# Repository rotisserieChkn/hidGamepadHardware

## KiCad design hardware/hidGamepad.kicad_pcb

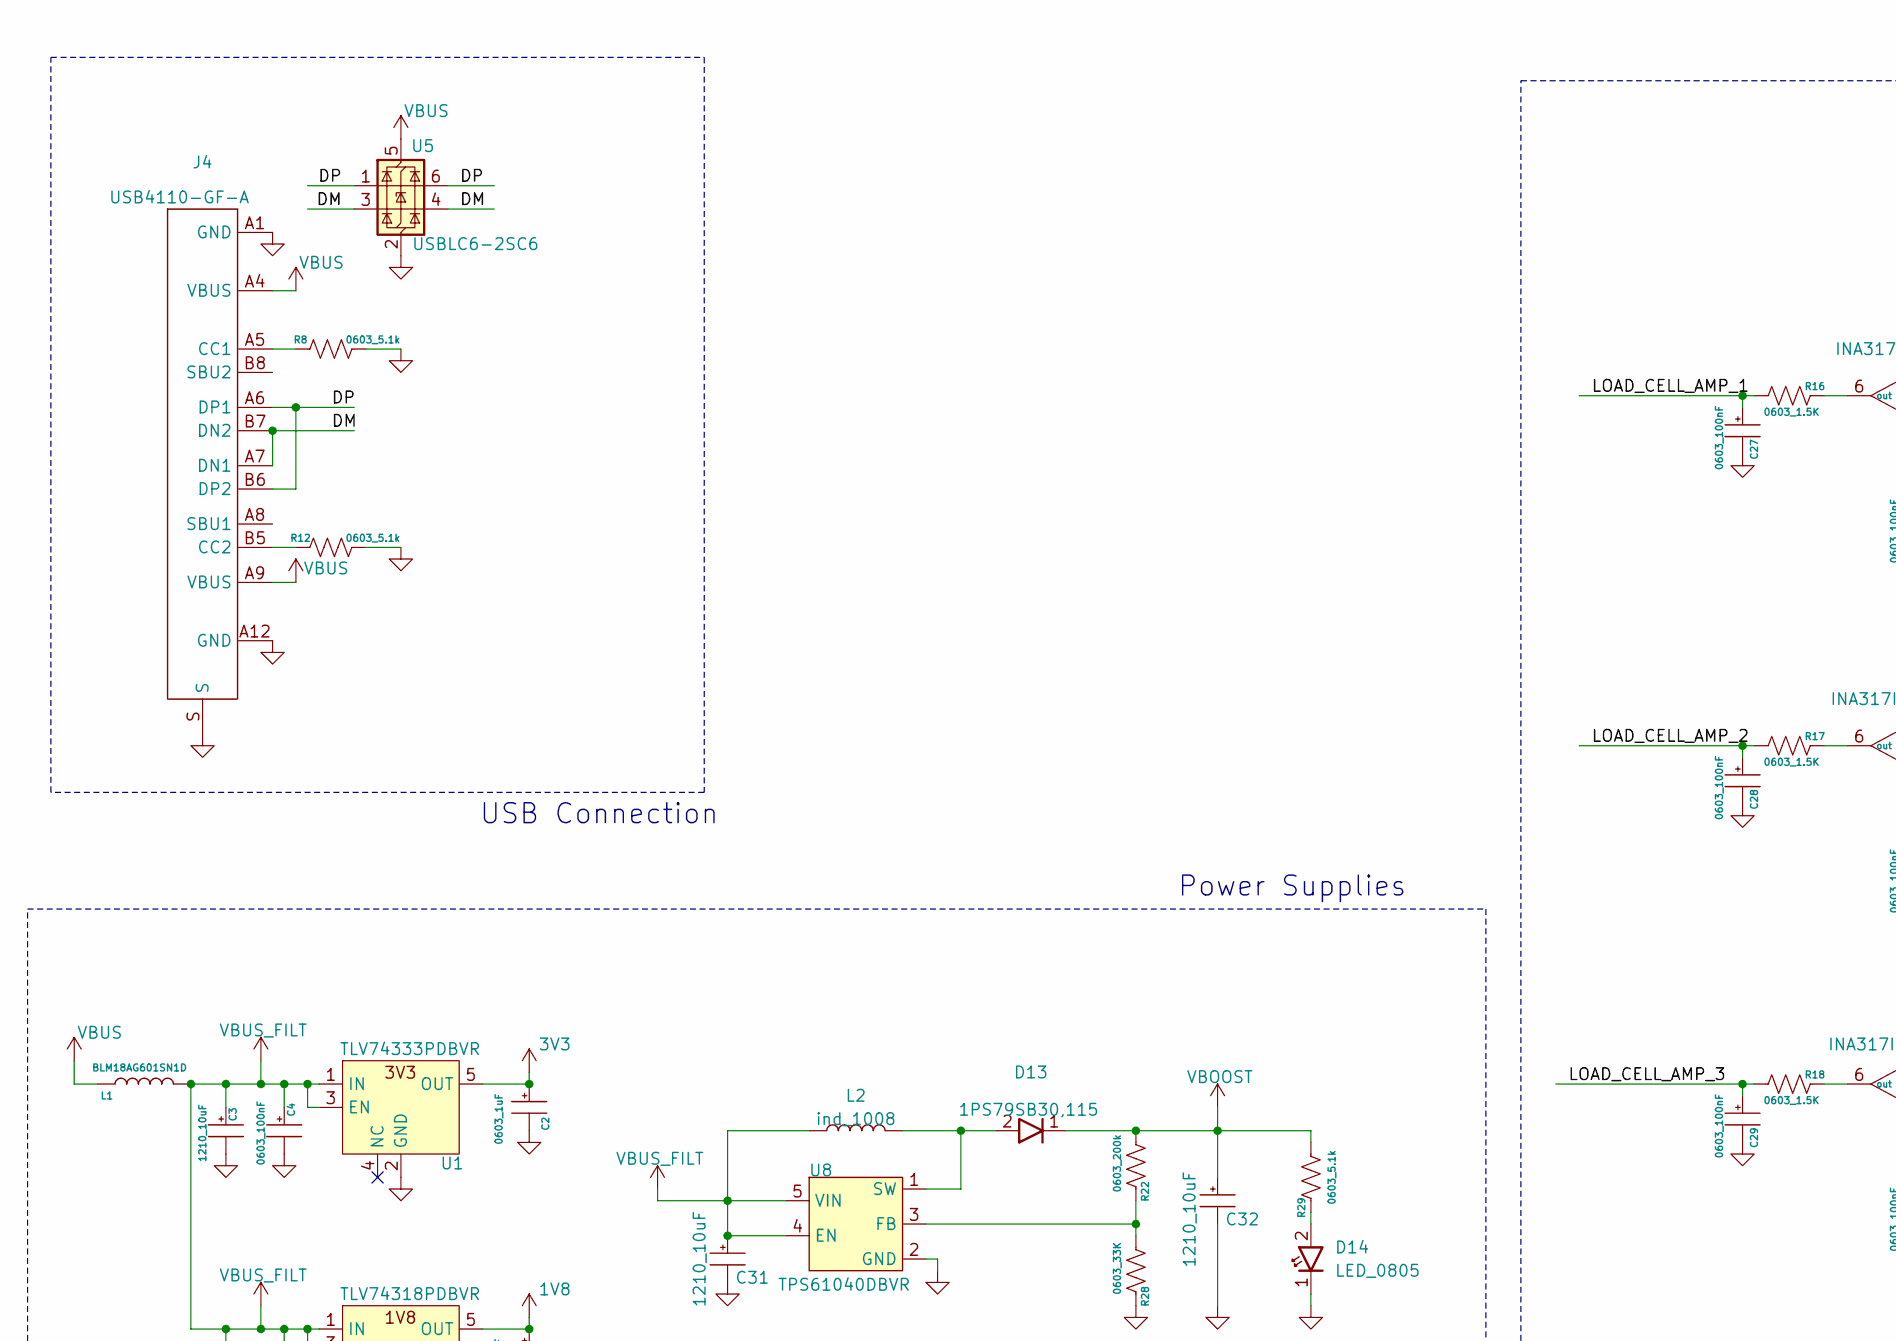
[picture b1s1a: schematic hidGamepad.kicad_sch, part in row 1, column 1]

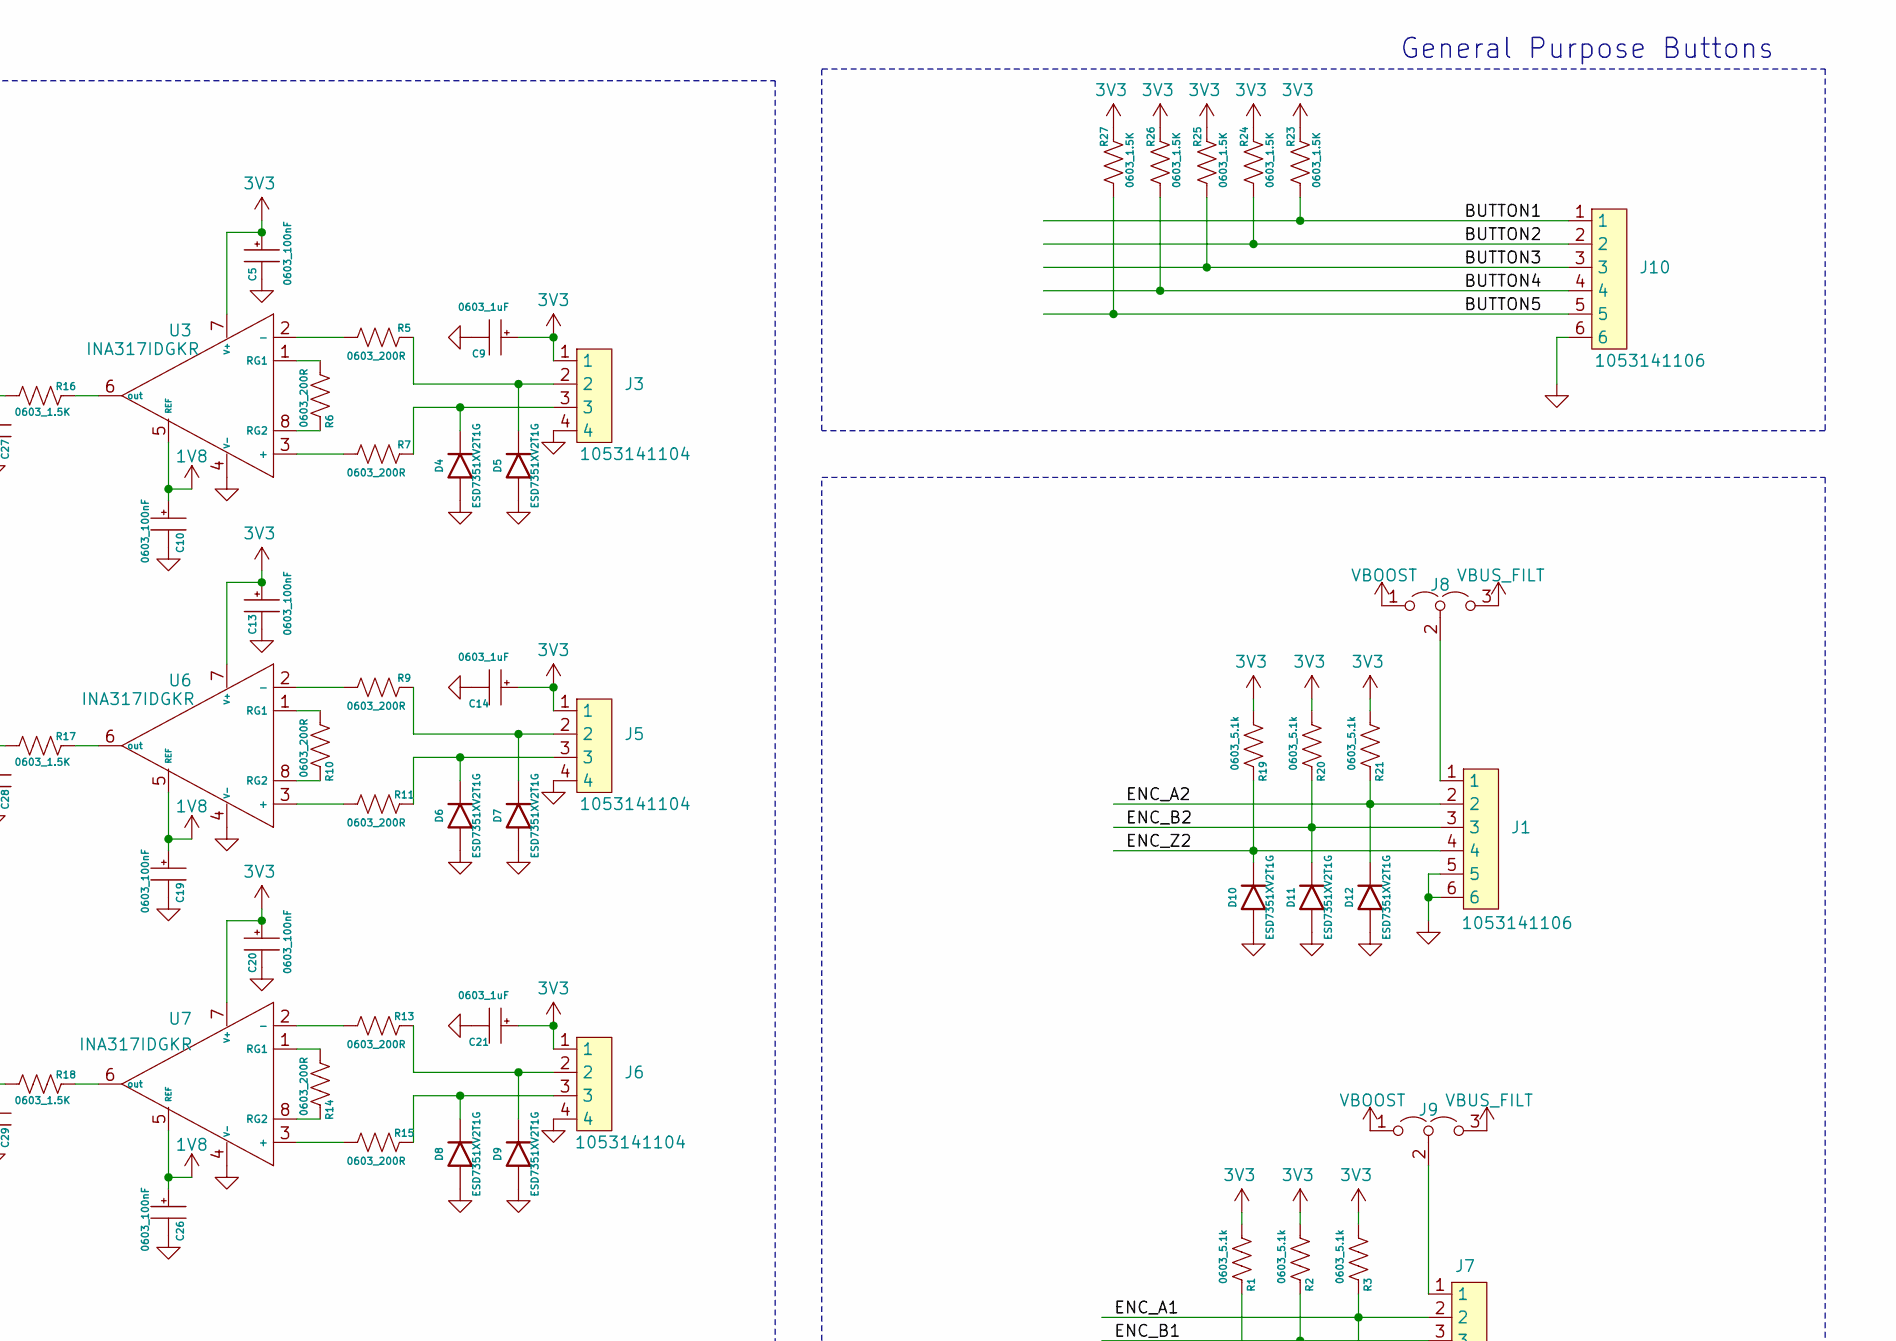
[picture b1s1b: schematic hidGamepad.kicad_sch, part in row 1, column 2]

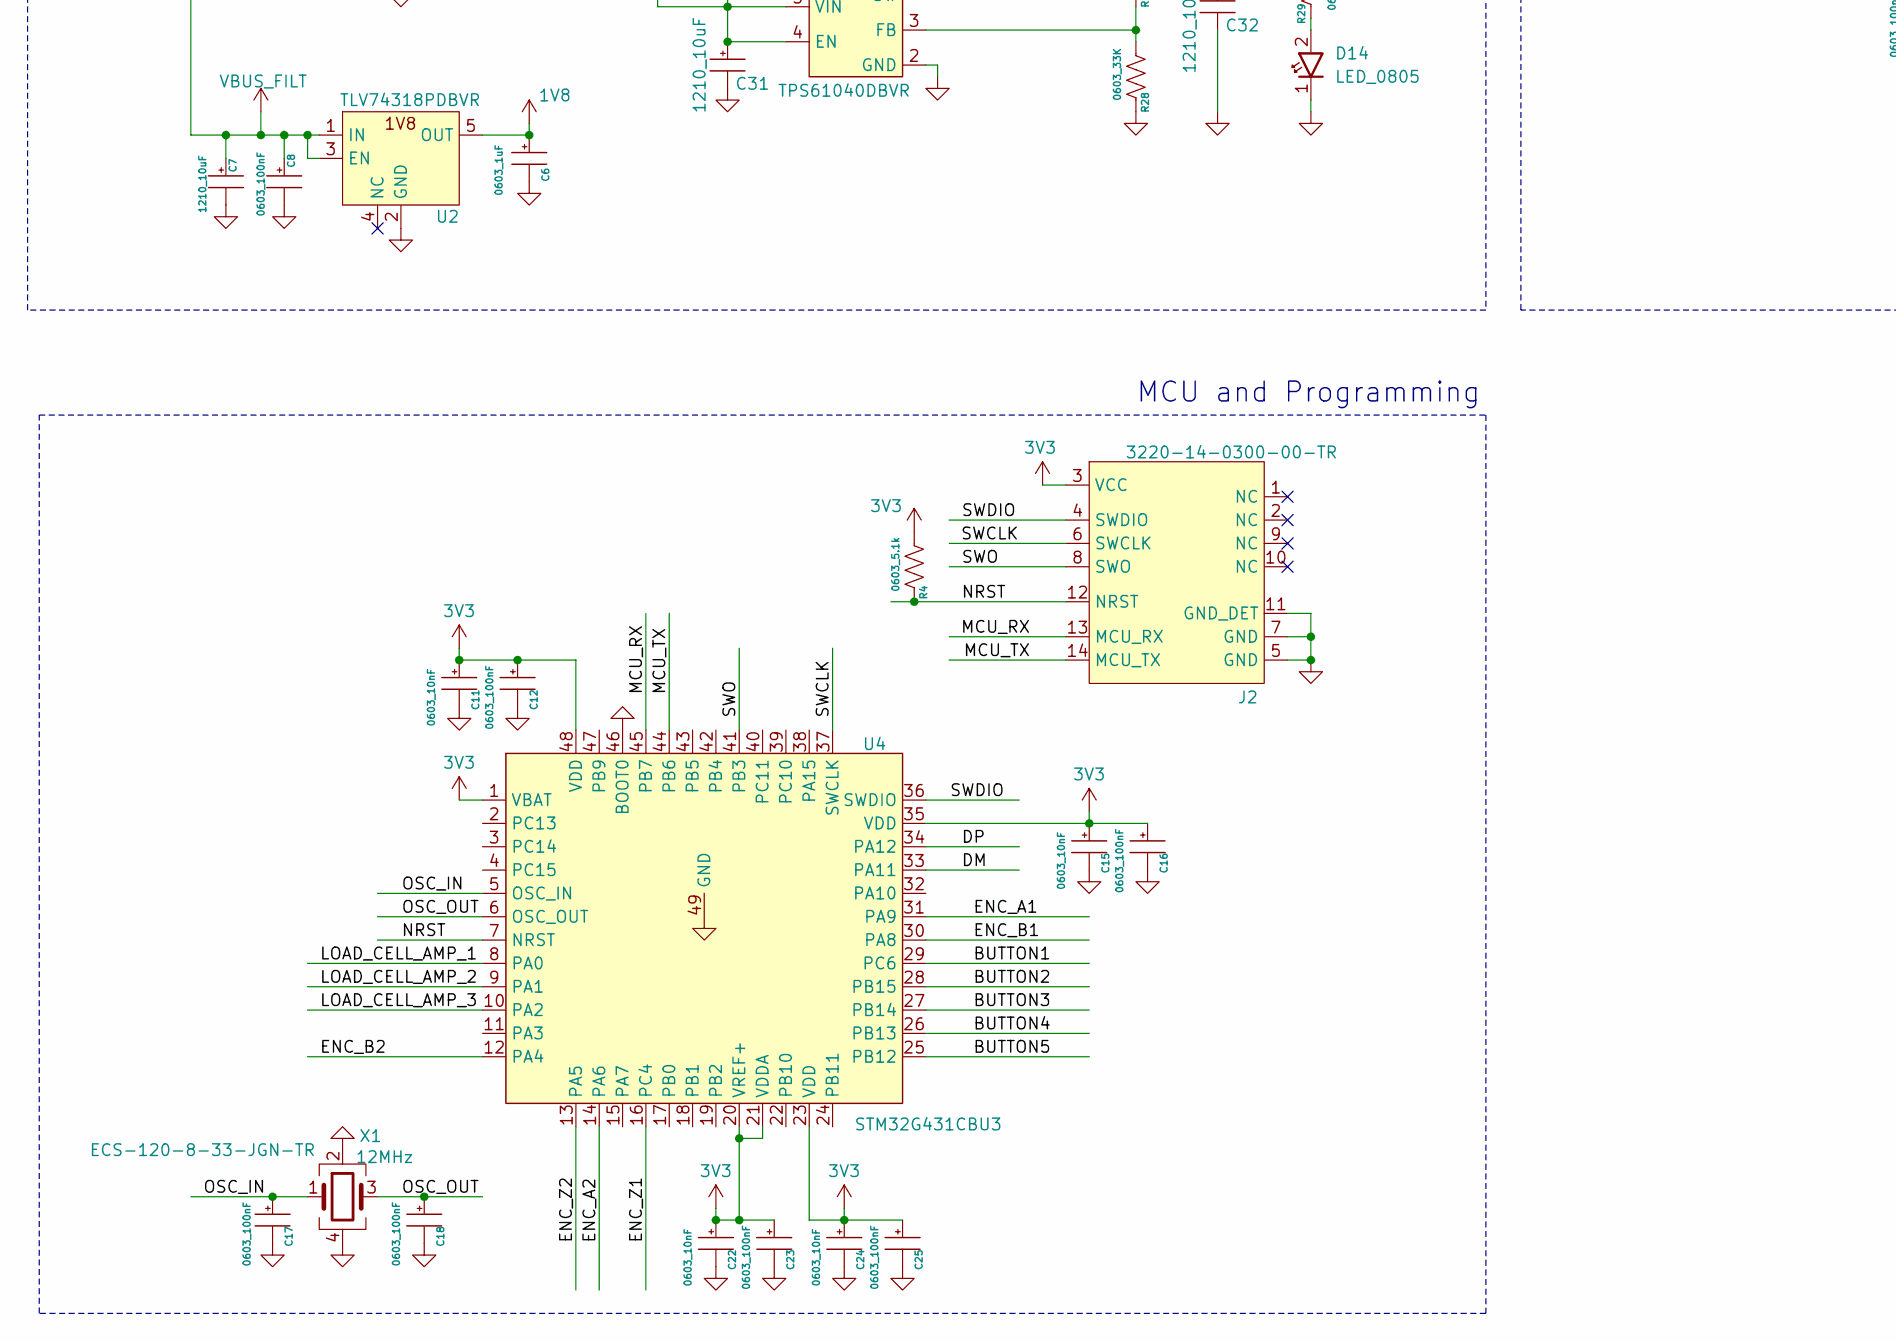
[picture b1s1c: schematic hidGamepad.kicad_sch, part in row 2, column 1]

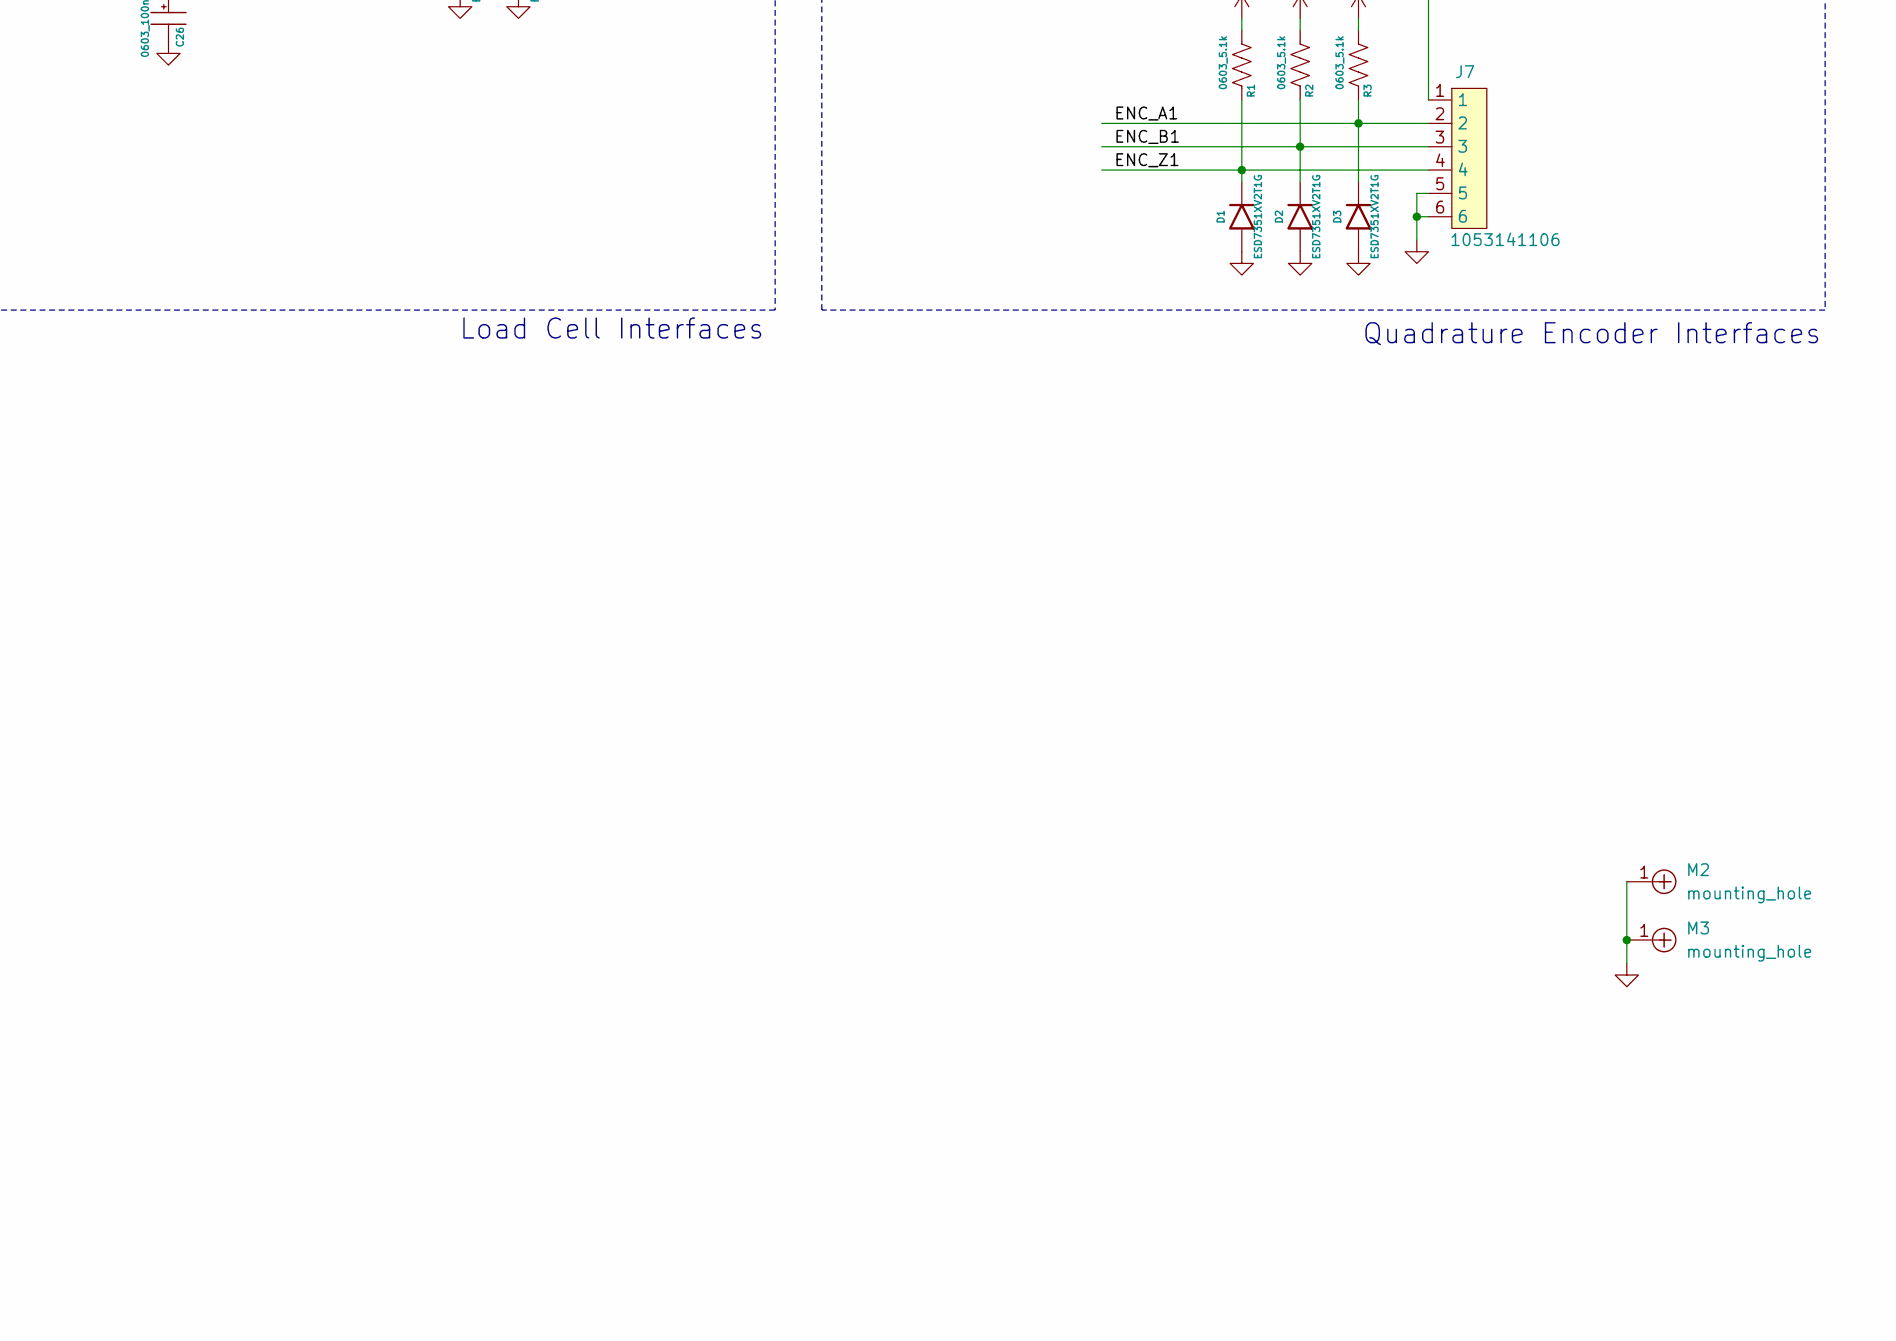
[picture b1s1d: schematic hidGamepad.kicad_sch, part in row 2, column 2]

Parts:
C2, C6, C9, C14, C21: 0603_1uF; C_0603_1608Metric
C3, C7, C31, C32: 1210_10uF; C_1210_3225Metric
C4, C5, C8, C10, C12, C13, C16, C17, C18, C19, C20, C23, C25, C26, C27, C28, C29: 0603_100nF; C_0603_1608Metric
C11, C15, C22, C24: 0603_10nF; C_0603_1608Metric
D1, D2, D3, D4, D5, D6, D7, D8, D9, D10, D11, D12: ESD7351XV2T1G; D_SOD-523; MFG_PN ESD7351XV2T1G
D13: 1PS79SB30,115; D_SOD-523; MFG_PN 1PS79SB30,115
D14: LED_0805; R_0805_2012Metric
J1, J7, J10: 1053141106; nanofit_2x3_1053141106; MFG_PN 1053141106
J2: 3220-14-0300-00-TR; SAMTEC_FTSH-107-01-L-DV-K-A; MFG_PN 3220-14-0300-00-TR
J3, J5, J6: 1053141104; nanofit_2x2_1053141104; MFG_PN 1053141104
J4: USB4110-GF-A; MFG_PN USB4110-GF-A
J8, J9: PinHeader_1x03_P2.54mm_Vertical
L1: BLM18AG601SN1D; R_0603_1608Metric; MFG_PN BLM18AG601SN1D
L2: ind_1008; L_1008_2520Metric
M2, M3: mounting_hole
R1, R2, R3, R4, R8, R12, R19, R20, R21, R29: 0603_5.1k; R_0603_1608Metric
R5, R6, R7, R9, R10, R11, R13, R14, R15: 0603_200R; R_0603_1608Metric
R16, R17, R18, R23, R24, R25, R26, R27: 0603_1.5K; R_0603_1608Metric
R22: 0603_200k; R_0603_1608Metric
R28: 0603_33K; R_0603_1608Metric
U1: TLV74333PDBVR; SOT-23-5; MFG_PN TLV74333PDBVR
U2: TLV74318PDBVR; SOT-23-5; MFG_PN TLV74318PDBVR
U3, U6, U7: INA317IDGKR; VSSOP-8_3x3mm_P0.65mm; MFG_PN INA317IDGKR
U4: STM32G431CBU3; QFN-48-1EP_7x7mm_P0.5mm_EP5.6x5.6mm_PASTE; MFG_PN STM32G431CBU3
U5: USBLC6-2SC6; SOT-23-6; MFG_PN USBLC6-2SC6
U8: TPS61040DBVR; SOT-23-5; MFG_PN TPS61040DBVR
X1: 12MHz; ECS-80-10-33-CHN-TR; MFG_PN ECS-120-8-33-JGN-TR

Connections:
1V8: C6.1, C10.1, C19.1, C26.1, U2.5 (OUT), U3.5 (REF), U6.5 (REF), U7.5 (REF)
3V3: C2.1, C5.1, C9.1, C11.1, C12.1, C13.1, C14.1, C15.1, C16.1, C20.1, C21.1, C22.1, C23.1, C24.1, C25.1, J2.3 (VCC), J3.1, J5.1, J6.1, R1.2, R2.2, R3.2, R4.2, R19.2, R20.2, R21.2, R23.1, R24.1, R25.1, R26.1, R27.1, U1.5 (OUT), U3.7 (V+), U4.1 (VBAT), U4.20 (VREF+), U4.21 (VDDA), U4.23 (VDD), U4.35 (VDD), U4.48 (VDD), U6.7 (V+), U7.7 (V+)
/BUTTON1: J10.1, R23.2, U4.29 (PC6)
/BUTTON2: J10.2, R24.2, U4.28 (PB15)
/BUTTON3: J10.3, R25.2, U4.27 (PB14)
/BUTTON4: J10.4, R26.2, U4.26 (PB13)
/BUTTON5: J10.5, R27.2, U4.25 (PB12)
/DM: J4.A7 (DN1), J4.B7 (DN2), U4.33 (PA11), U5.3 (I/O2), U5.4 (I/O2)
/DP: J4.A6 (DP1), J4.B6 (DP2), U4.34 (PA12), U5.1 (I/O1), U5.6 (I/O1)
/ENC_A1: D3.1, J7.2, R3.1, U4.31 (PA9)
/ENC_A2: D12.1, J1.2, R21.1, U4.14 (PA6)
/ENC_B1: D2.1, J7.3, R2.1, U4.30 (PA8)
/ENC_B2: D11.1, J1.3, R20.1, U4.12 (PA4)
/ENC_Z1: D1.1, J7.4, R1.1, U4.16 (PC4)
/ENC_Z2: D10.1, J1.4, R19.1, U4.13 (PA5)
/LOAD_CELL_AMP_1: C27.1, R16.2, U4.8 (PA0)
/LOAD_CELL_AMP_2: C28.1, R17.2, U4.9 (PA1)
/LOAD_CELL_AMP_3: C29.1, R18.2, U4.10 (PA2)
/MCU_RX: J2.13 (MCU_RX), U4.45 (PB7)
/MCU_TX: J2.14 (MCU_TX), U4.44 (PB6)
/NRST: J2.12 (NRST), R4.1, U4.7 (NRST)
/OSC_IN: C17.1, U4.5 (OSC_IN), X1.1
/OSC_OUT: C18.1, U4.6 (OSC_OUT), X1.3
/SWCLK: J2.6 (SWCLK), U4.37 (SWCLK)
/SWDIO: J2.4 (SWDIO), U4.36 (SWDIO)
/SWO: J2.8 (SWO), U4.41 (PB3)
GND: C2.2, C3.2, C4.2, C5.2, C6.2, C7.2, C8.2, C9.2, C10.2, C11.2, C12.2, C13.2, C14.2, C15.2, C16.2, C17.2, C18.2, C19.2, C20.2, C21.2, C22.2, C23.2, C24.2, C25.2, C26.2, C27.2, C28.2, C29.2, C31.2, C32.2, D1.2, D2.2, D3.2, D4.2, D5.2, D6.2, D7.2, D8.2, D9.2, D10.2, D11.2, D12.2, D14.1, J1.5, J1.6, J2.5 (GND), J2.7 (GND), J2.11 (GND_DET), J3.4, J4.A1 (GND), J4.A12 (GND), J4.S, J5.4, J6.4, J7.5, J7.6, J10.6, M2.1, M3.1, R8.2, R12.2, R28.1, U1.2 (GND), U2.2 (GND), U3.4 (V-), U4.46 (BOOT0), U4.49 (GND), U5.2 (GND), U6.4 (V-), U7.4 (V-), U8.2 (GND), X1.2, X1.4
unnamed: D4.1, J3.3, R7.1
unnamed: D5.1, J3.2, R5.1
unnamed: D6.1, J5.3, R11.1
unnamed: D7.1, J5.2, R9.1
unnamed: D8.1, J6.3, R15.1
unnamed: D9.1, J6.2, R13.1
unnamed: D14.2, R29.1
unnamed: J4.A5 (CC1), R8.1
unnamed: J4.B5 (CC2), R12.1
unnamed: J1.1, J8.2 (C)
unnamed: J7.1, J9.2 (C)
unnamed: R7.2, U3.3 (+)
unnamed: R5.2, U3.2 (-)
unnamed: R6.2, U3.1 (RG1)
unnamed: R6.1, U3.8 (RG2)
unnamed: R16.1, U3.6 (out)
unnamed: R11.2, U6.3 (+)
unnamed: R9.2, U6.2 (-)
unnamed: R10.2, U6.1 (RG1)
unnamed: R10.1, U6.8 (RG2)
unnamed: R17.1, U6.6 (out)
unnamed: R15.2, U7.3 (+)
unnamed: R13.2, U7.2 (-)
unnamed: R14.2, U7.1 (RG1)
unnamed: R14.1, U7.8 (RG2)
unnamed: R18.1, U7.6 (out)
unnamed: R22.1, R28.2, U8.3 (FB)
unnamed: D13.2, L2.2, U8.1 (SW)
VBOOST: C32.1, D13.1, J8.1 (A), J9.1 (A), R22.2, R29.2
VBUS: J4.A4 (VBUS), J4.A9 (VBUS), L1.1, U5.5 (VBUS)
VBUS_FILT: C3.1, C4.1, C7.1, C8.1, C31.1, J8.3 (B), J9.3 (B), L1.2, L2.1, U1.1 (IN), U1.3 (EN), U2.1 (IN), U2.3 (EN), U8.4 (EN), U8.5 (VIN)

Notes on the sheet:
General Purpose Buttons
Power Supplies
Load Cell Interfaces
USB Connection
MCU and Programming
Quadrature Encoder Interfaces

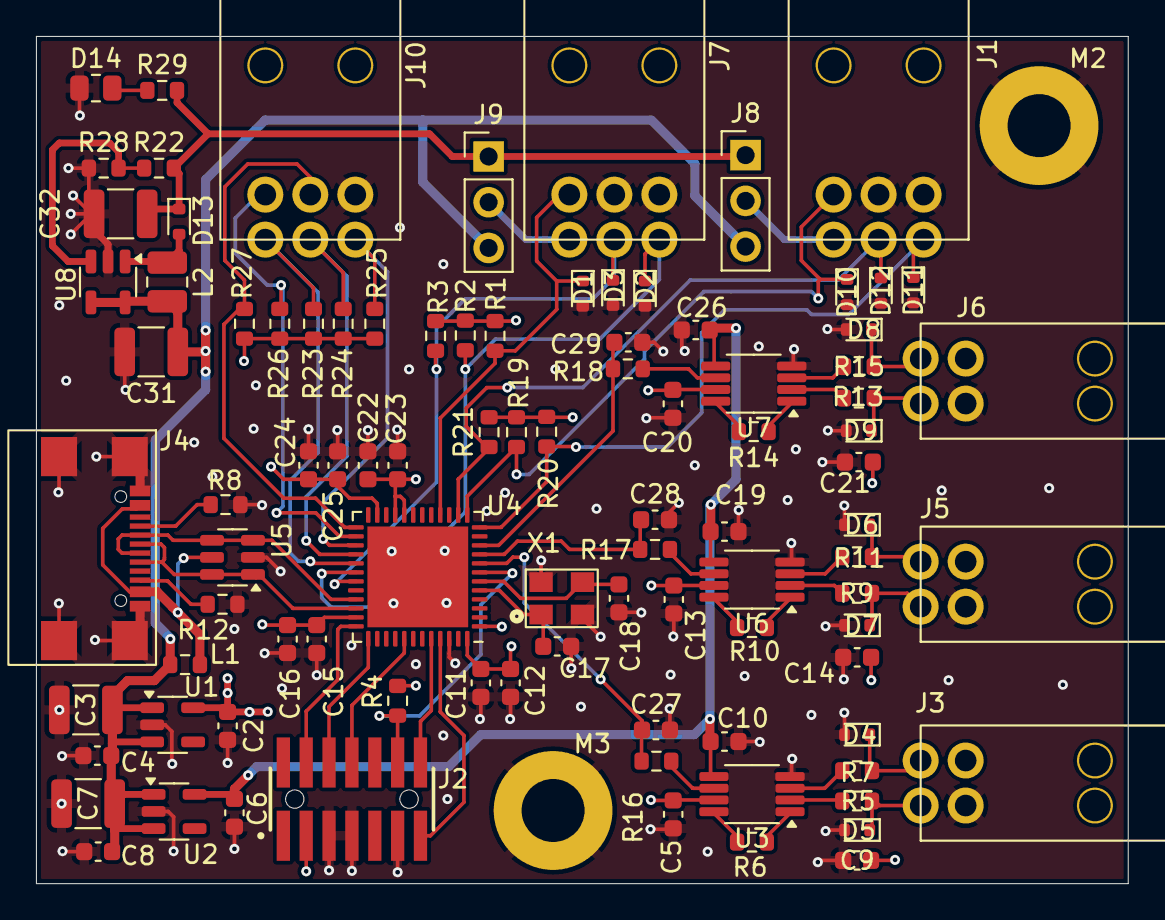
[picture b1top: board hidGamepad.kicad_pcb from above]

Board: 4 copper layers, 60.7 x 47.1 mm, 96 parts (0 on the bottom side), 58 nets.

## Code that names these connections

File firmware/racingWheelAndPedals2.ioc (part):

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Mcu.Name=STM32G431C(6-8-B)Ux
Mcu.Package=UFQFPN48
Mcu.UserName=STM32G431CBUx
PA0.Mode=IN1-Single-Ended
PA0.Signal=ADC1_IN1
PA1.Mode=IN2-Single-Ended
PA1.Signal=ADC1_IN2
PA11.Mode=Device
PA11.Signal=USB_DM
PA12.Mode=Device
PA12.Signal=USB_DP
PA13.Mode=Trace_Asynchronous_SW
PA13.Signal=SYS_JTMS-SWDIO
PA14.Mode=Trace_Asynchronous_SW
PA14.Signal=SYS_JTCK-SWCLK
PA2.Mode=IN3-Single-Ended
PA2.Signal=ADC1_IN3
PA4.Signal=S_TIM3_CH2
PA6.Signal=S_TIM3_CH1
PA8.Signal=S_TIM1_CH1
PA9.Signal=S_TIM1_CH2
PB12.Signal=GPIO_Input
PB13.Signal=GPIO_Input
PB14.Signal=GPIO_Input
PB15.Signal=GPIO_Input
PB3.Mode=Trace_Asynchronous_SW
PB3.Signal=SYS_JTDO-SWO
PB6.Mode=Asynchronous
PB6.Signal=USART1_TX
PB7.Mode=Asynchronous
PB7.Signal=USART1_RX
PC6.Signal=GPIO_Input
PF0-OSC_IN.Mode=HSE-External-Oscillator
PF0-OSC_IN.Signal=RCC_OSC_IN
PF1-OSC_OUT.Mode=HSE-External-Oscillator
PF1-OSC_OUT.Signal=RCC_OSC_OUT
RCC.HSE_VALUE=12000000
RCC.SYSCLKFreq_VALUE=144000000
RCC.SYSCLKSource=RCC_SYSCLKSOURCE_PLLCLK
board=custom
